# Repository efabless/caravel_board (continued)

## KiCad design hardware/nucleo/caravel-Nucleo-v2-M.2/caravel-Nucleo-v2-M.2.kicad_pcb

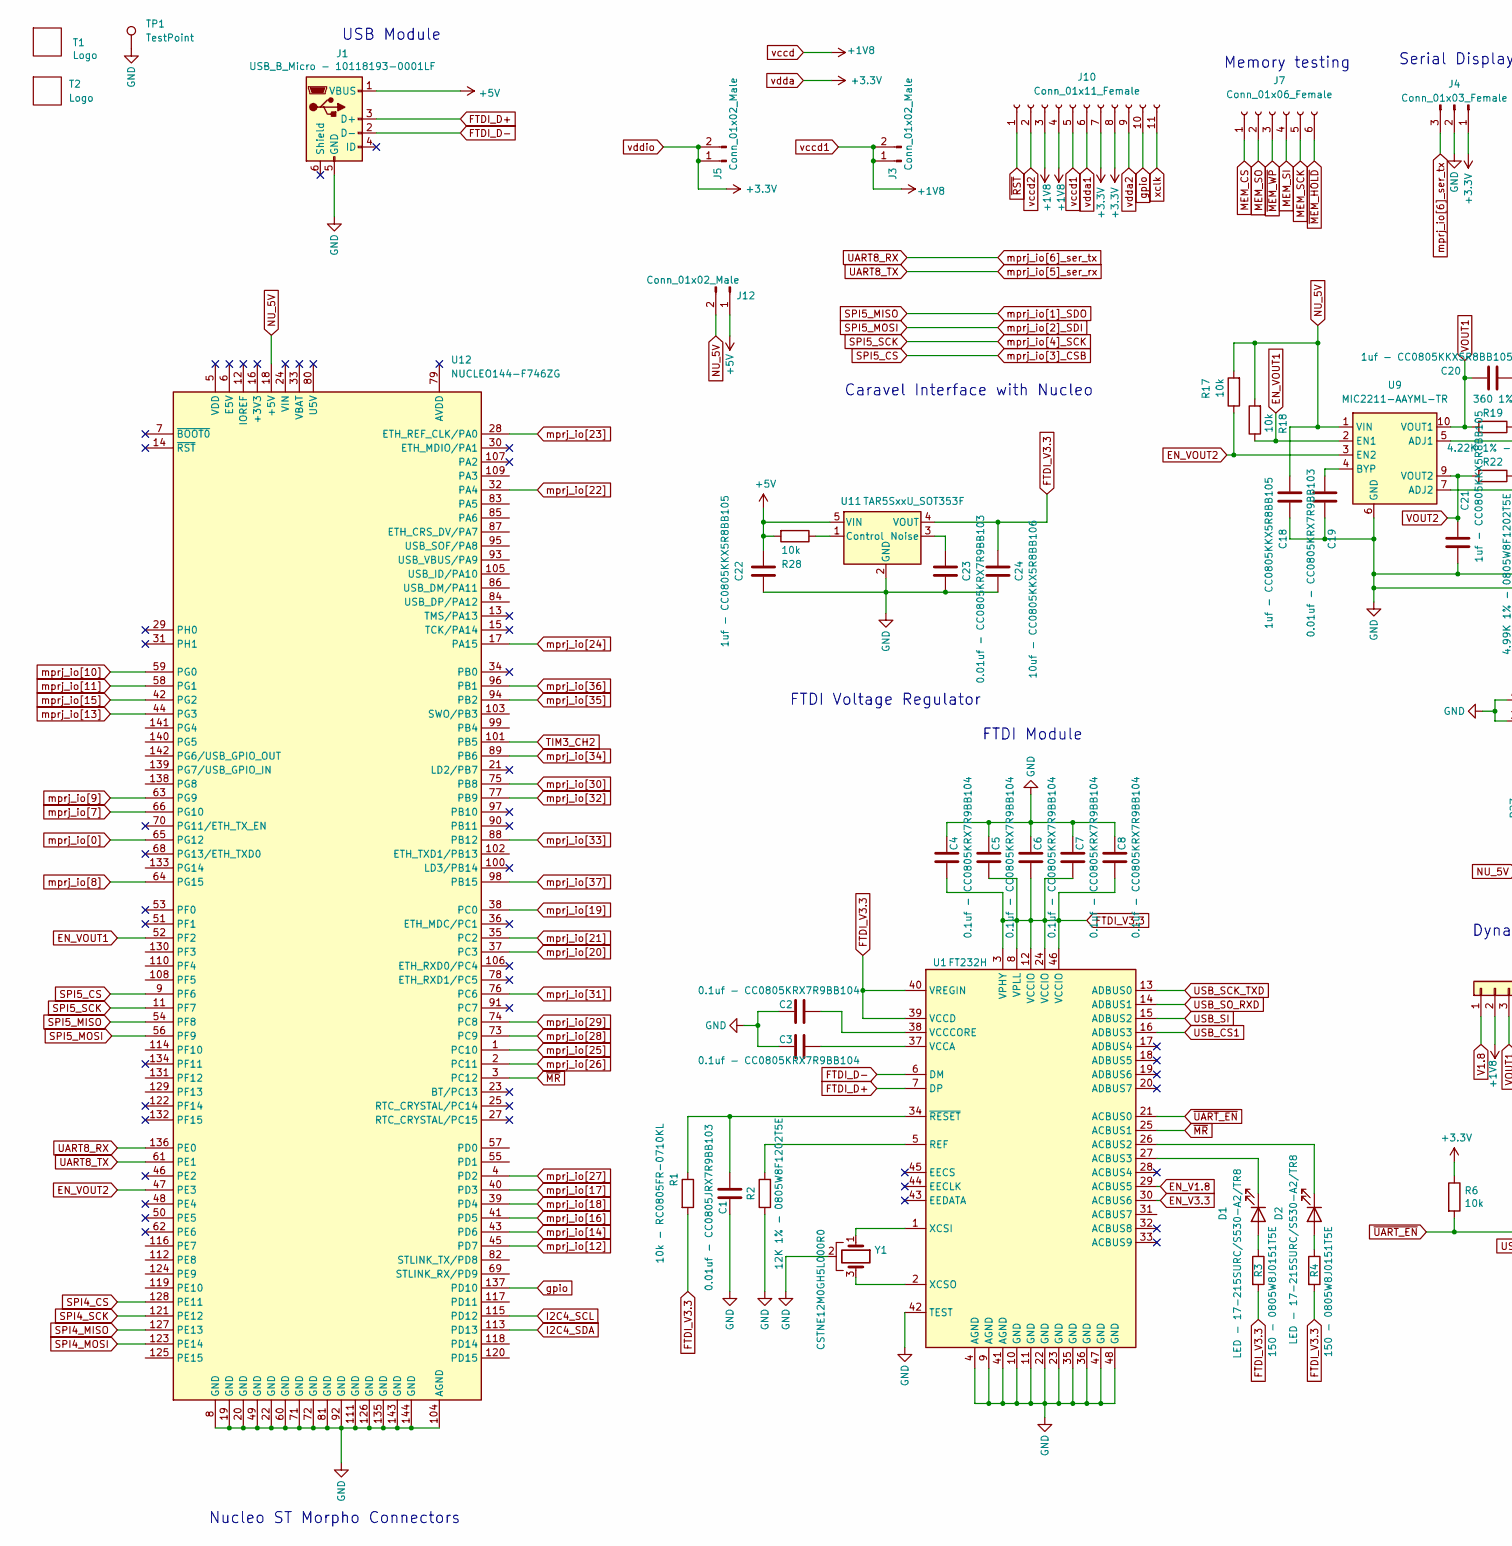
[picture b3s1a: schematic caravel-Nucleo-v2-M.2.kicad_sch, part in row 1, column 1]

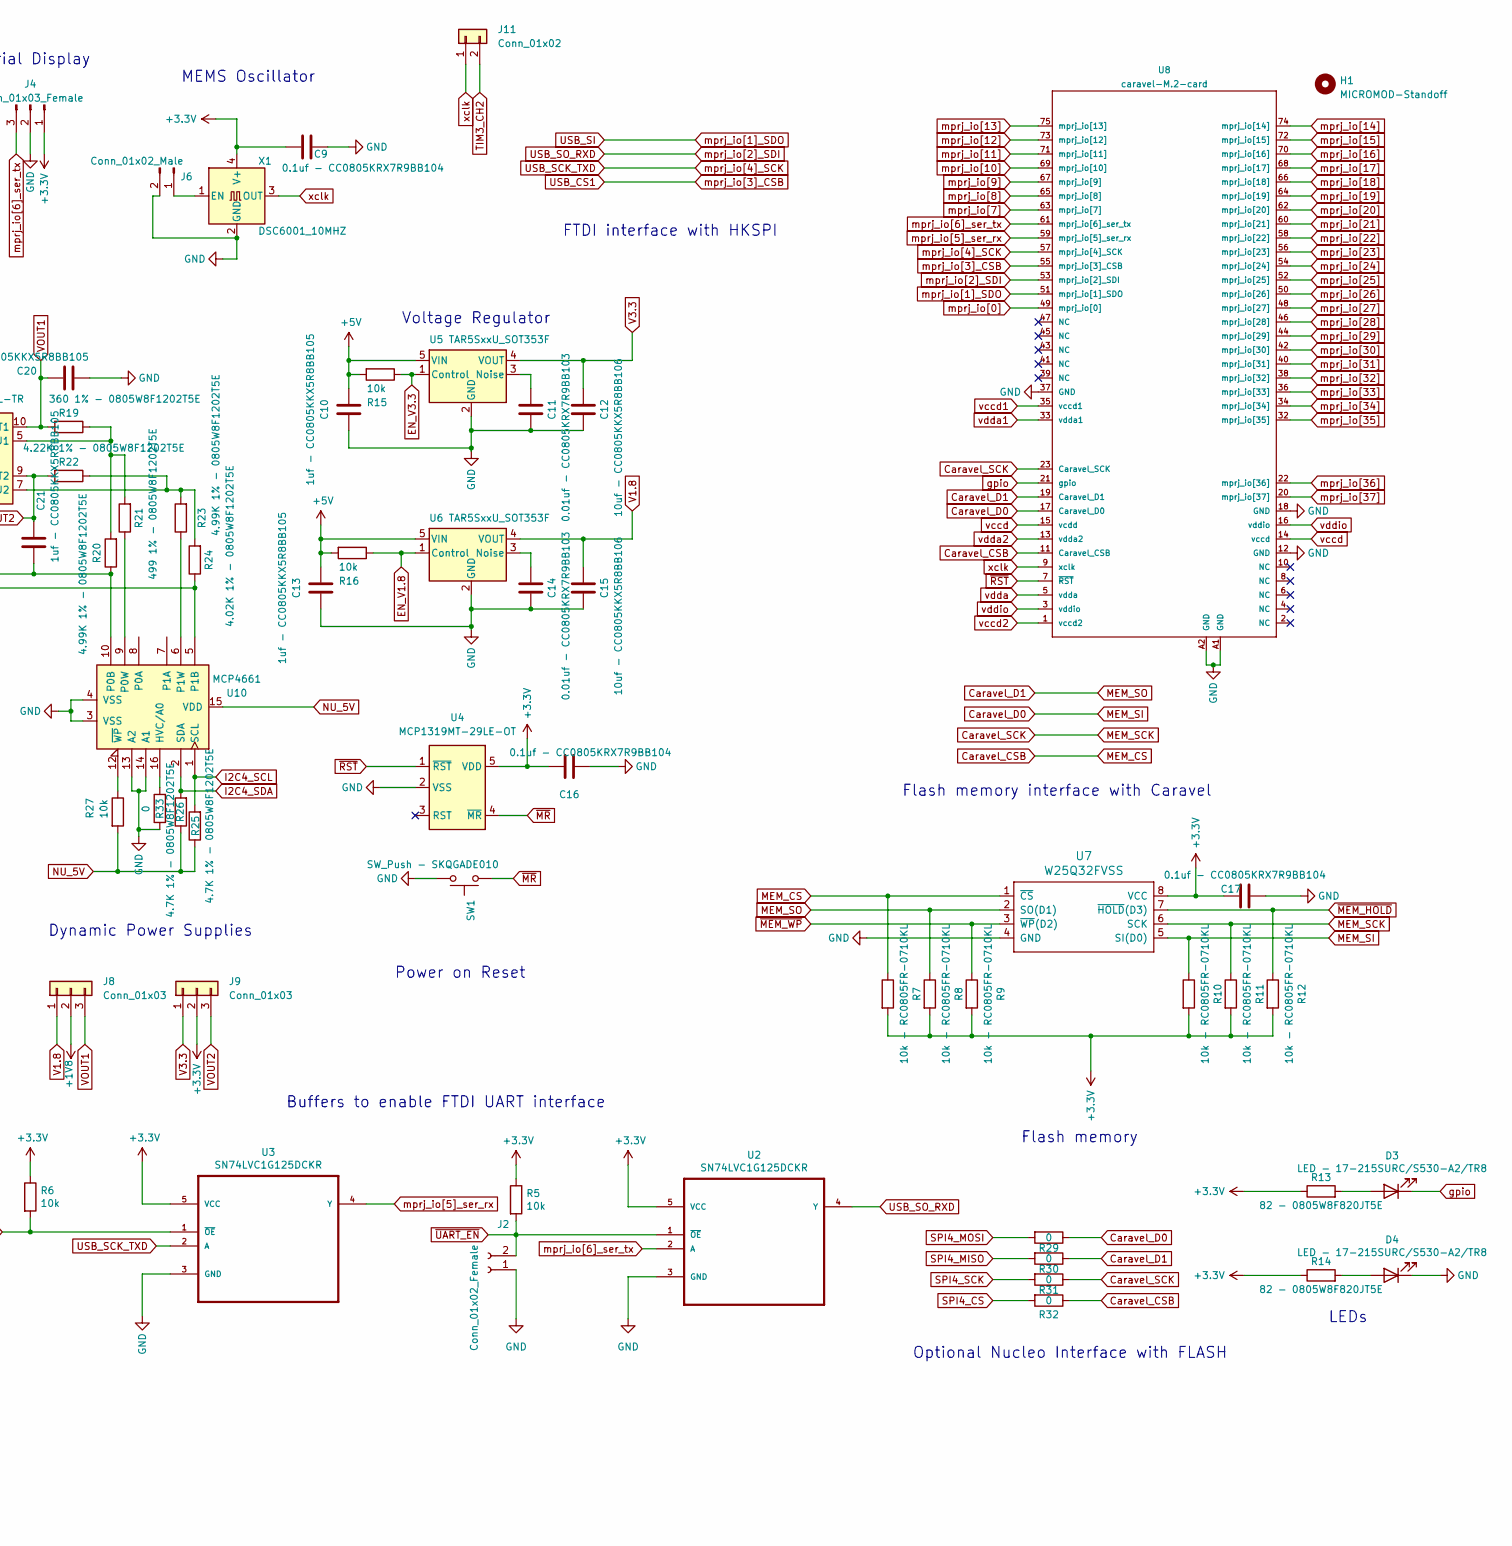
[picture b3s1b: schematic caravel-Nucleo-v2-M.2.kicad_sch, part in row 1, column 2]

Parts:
C1: 0.01uf - CC0805JRX7R9BB103; C_0805_2012Metric
C2, C3, C4, C5, C6, C7, C8, C9, C16, C17: 0.1uf - CC0805KRX7R9BB104; C_0805_2012Metric
C10, C13, C18, C20, C21, C22: 1uf - CC0805KKX5R8BB105; C_0805_2012Metric
C11, C14, C19, C23: 0.01uf - CC0805KRX7R9BB103; C_0805_2012Metric
C12, C15, C24: 10uf - CC0805KKX5R8BB106; C_0805_2012Metric
D1, D2, D3, D4: LED - 17-215SURC/S530-A2/TR8; LED_1206_3216Metric
H1: MICROMOD-Standoff; MicroMod-Standoff
J1: USB_B_Micro - 10118193-0001LF; FCI_10118193-0001LF
J2: Conn_01x02_Female; PinHeader_1x02_P2.54mm_Vertical
J3, J5, J6, J12: Conn_01x02_Male; PinHeader_1x02_P2.54mm_Vertical
J4: Conn_01x03_Female; PinHeader_1x03_P2.54mm_Vertical
J7: Conn_01x06_Female; PinHeader_1x06_P2.54mm_Vertical
J8, J9: Conn_01x03; PinHeader_1x03_P2.54mm_Vertical
J10: Conn_01x11_Female; PinHeader_1x11_P2.54mm_Vertical
J11: Conn_01x02; PinHeader_1x02_P2.54mm_Vertical
R1, R7, R8, R9, R10, R11, R12: 10k - RC0805FR-0710KL; R_0805_2012Metric
R2: 12K 1% - 0805W8F1202T5E; R_0805_2012Metric
R3, R4: 150 - 0805W8J0151T5E; R_0805_2012Metric
R5, R6, R15, R16, R17, R18, R27, R28: 10k; R_0805_2012Metric
R13, R14: 82 - 0805W8F820JT5E; R_0805_2012Metric
R19: 360 1% - 0805W8F1202T5E; R_0805_2012Metric
R20, R23: 4.99K 1% - 0805W8F1202T5E; R_0805_2012Metric
R21: 499 1% - 0805W8F1202T5E; R_0805_2012Metric
R22: 4.22K 1% - 0805W8F1202T5E; R_0805_2012Metric
R24: 4.02K 1% - 0805W8F1202T5E; R_0805_2012Metric
R25, R26: 4.7K 1% - 0805W8F1202T5E; R_0805_2012Metric
R29, R30, R31, R32, R33: 0; R_0805_2012Metric
SW1: SW_Push - SKQGADE010; SW4-SMD-5.2X5.2X1.5MM
T1: Logo; logo
T2: Logo; ef_logo
TP1: TestPoint; TestPoint_Bridge_Pitch2.54mm_Drill1.0mm
U1: FT232H; QFN-48-1EP_8x8mm_P0.5mm_EP6.2x6.2mm
U2, U3: SN74LVC1G125DCKR; SOT65P210X110-5N
U4: MCP1319MT-29LE-OT; PoR_5_SOT23
U5, U6, U11: TAR5SxxU_SOT353F; SOT-353F
U7: W25Q32FVSS; SOIC127P790X216-8N
U8: caravel-M.2-card; M.2-CONNECTOR-E
U9: MIC2211-AAYML-TR; DFN-10-1EP_3x3mm_P0.5mm_EP1.65x2.38mm
U10: MCP4661; QFN-16-1EP_5x5mm_P0.8mm_EP2.7x2.7mm
U12: NUCLEO144-F746ZG; ST_Morpho_Connector_144_STLink
X1: DSC6001_10MHZ; DSC6001JE1A-010.0000
Y1: CSTNE12M0GH5L000R0

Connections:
+5V: C10.2, C13.2, C22.2, J1.1 (VBUS), J12.1, R15.2, R16.2, R28.2, U5.5 (VIN), U6.5 (VIN), U11.5 (VIN)
Caravel_CSB: J7.1, R7.1, R32.1, U7.1 (~CS), U8.11 (Caravel_CSB)
Caravel_D0: J7.4, R10.1, R29.1, U7.5 (SI(D0)), U8.17 (Caravel_D0)
Caravel_D1: J7.2, R8.1, R30.1, U7.2 (SO(D1)), U8.19 (Caravel_D1)
Caravel_SCK: J7.5, R11.1, R31.1, U7.6 (SCK), U8.23 (Caravel_SCK)
EN_V1.8: R16.1, U1.29 (ACBUS5), U6.1 (Control)
EN_V3.3: R15.1, U1.30 (ACBUS6), U5.1 (Control)
EN_VOUT1: R18.1, U9.2 (EN1), U12.52 (PF2)
EN_VOUT2: R17.1, U9.3 (EN2), U12.47 (PE3)
FTDI_D+: J1.3 (D+), U1.7 (DP)
FTDI_D-: J1.2 (D-), U1.6 (DM)
FTDI_V3.3: C4.2, C5.2, C6.2, C7.2, C8.2, C24.2, R1.2, R3.2, R4.2, U1.3 (VPHY), U1.8 (VPLL), U1.12 (VCCIO), U1.24 (VCCIO), U1.39 (VCCD), U1.40 (VREGIN), U1.46 (VCCIO), U11.4 (VOUT)
GND: C1.1, C2.1, C3.1, C4.1, C5.1, C6.1, C7.1, C8.1, C9.1, C10.1, C11.2, C12.1, C13.1, C14.2, C15.1, C16.1, C17.2, C18.1, C19.2, C20.2, C21.2, C22.1, C23.2, C24.1, D4.1 (K), J1.5 (GND), J2.1, J4.2, J6.2, R2.1, R20.1, R24.1, R33.1, SW1.2, TP1.1, U1.4 (AGND), U1.9 (AGND), U1.10 (GND), U1.11 (GND), U1.22 (GND), U1.23 (GND), U1.35 (GND), U1.36 (GND), U1.41 (AGND), U1.42 (TEST), U1.47 (GND), U1.48 (GND), U2.3 (GND), U3.3 (GND), U4.2 (VSS), U5.2 (GND), U6.2 (GND), U7.4 (GND), U8.12 (GND), U8.18 (GND), U8.37 (GND), U8.A1 (GND), U8.A2 (GND), U9.6 (GND), U10.3 (VSS), U10.4 (VSS), U10.5 (P1B), U10.10 (P0B), U10.13 (A2), U10.14 (A1), U11.2 (GND), U12.8 (GND), U12.19 (GND), U12.20 (GND), U12.22 (GND), U12.49 (GND), U12.60 (GND), U12.71 (GND), U12.72 (GND), U12.81 (GND), U12.92 (GND), U12.104 (AGND), U12.111 (GND), U12.126 (GND), U12.135 (GND), U12.143 (GND), U12.144 (GND), X1.2 (GND), Y1.2
I2C4_SCL: R25.2, U10.1 (SCL), U12.115 (PD12)
I2C4_SDA: R26.2, U10.2 (SDA), U12.113 (PD13)
NU_5V: C18.2, J12.2, R17.2, R18.2, R25.1, R26.1, R27.2, U9.1 (VIN), U10.15 (VDD), U12.18 (+5V)
unnamed: D1.2 (A), R3.1
unnamed: D1.1 (K), U1.27 (ACBUS3)
unnamed: D2.2 (A), R4.1
unnamed: D2.1 (K), U1.26 (ACBUS2)
unnamed: D3.2 (A), R13.2
unnamed: D4.2 (A), R14.2
unnamed: J6.1, X1.1 (EN)
unnamed: R2.2, U1.5 (REF)
unnamed: C3.2, U1.37 (VCCA)
unnamed: C2.2, U1.38 (VCCCORE)
unnamed: U1.1 (XCSI), Y1.1
unnamed: U1.2 (XCSO), Y1.3
unnamed: C1.2, R1.1, U1.34 (~RESET)
unnamed: C11.1, U5.3 (Noise)
unnamed: C14.1, U6.3 (Noise)
unnamed: R19.1, R20.2, R21.2, U9.5 (ADJ1)
unnamed: R22.1, R23.2, R24.2, U9.7 (ADJ2)
unnamed: C19.1, U9.4 (BYP)
unnamed: R33.2, U10.16 (HVC/A0)
unnamed: R21.1, U10.9 (P0W)
unnamed: R23.1, U10.6 (P1W)
unnamed: R27.1, U10.12 (~WP)
unnamed: R28.1, U11.1 (Control)
unnamed: C23.1, U11.3 (Noise)
SPI4_CS: R32.2, U12.128 (PE11)
SPI4_MISO: R30.2, U12.127 (PE13)
SPI4_MOSI: R29.2, U12.123 (PE14)
SPI4_SCK: R31.2, U12.121 (PE12)
SPI5_CS: U1.16 (ADBUS3), U8.55 (mprj_io[3]_CSB), U12.9 (PF6)
SPI5_MISO: U1.15 (ADBUS2), U8.51 (mprj_io[1]_SDO), U12.54 (PF8)
SPI5_MOSI: U1.14 (ADBUS1), U2.4 (Y), U8.53 (mprj_io[2]_SDI), U12.56 (PF9)
SPI5_SCK: U1.13 (ADBUS0), U3.2 (A), U8.57 (mprj_io[4]_SCK), U12.11 (PF7)
TIM3_CH2: J11.2, U12.101 (PB5)
UART8_RX: J4.3, U2.2 (A), U8.61 (mprj_io[6]_ser_tx), U12.136 (PE0)
UART8_TX: U3.4 (Y), U8.59 (mprj_io[5]_ser_rx), U12.61 (PE1)
V1.8: C15.2, J8.1, U6.4 (VOUT)
V3.3: C12.2, J9.1, U5.4 (VOUT)
VOUT1: C20.1, J8.3, R19.2, U9.10 (VOUT1)
VOUT2: C21.1, J9.3, R22.2, U9.9 (VOUT2)
gpio: D3.1 (K), J10.10, U8.21 (gpio), U12.137 (PD10)
mprj_io[0]: U8.49 (mprj_io[0]), U12.65 (PG12)
mprj_io[7]: U8.63 (mprj_io[7]), U12.66 (PG10)
mprj_io[8]: U8.65 (mprj_io[8]), U12.64 (PG15)
mprj_io[9]: U8.67 (mprj_io[9]), U12.63 (PG9)
mprj_io[10]: U8.69 (mprj_io[10]), U12.59 (PG0)
mprj_io[11]: U8.71 (mprj_io[11]), U12.58 (PG1)
mprj_io[12]: U8.73 (mprj_io[12]), U12.45 (PD7)
mprj_io[13]: U8.75 (mprj_io[13]), U12.44 (PG3)
mprj_io[14]: U8.74 (mprj_io[14]), U12.43 (PD6)
mprj_io[15]: U8.72 (mprj_io[15]), U12.42 (PG2)
mprj_io[16]: U8.70 (mprj_io[16]), U12.41 (PD5)
mprj_io[17]: U8.68 (mprj_io[17]), U12.40 (PD3)
mprj_io[18]: U8.66 (mprj_io[18]), U12.39 (PD4)
mprj_io[19]: U8.64 (mprj_io[19]), U12.38 (PC0)
mprj_io[20]: U8.62 (mprj_io[20]), U12.37 (PC3)
mprj_io[21]: U8.60 (mprj_io[21]), U12.35 (PC2)
mprj_io[22]: U8.58 (mprj_io[22]), U12.32 (PA4)
mprj_io[23]: U8.56 (mprj_io[23]), U12.28 (ETH_REF_CLK/PA0)
mprj_io[24]: U8.54 (mprj_io[24]), U12.17 (PA15)
mprj_io[25]: U8.52 (mprj_io[25]), U12.1 (PC10)
mprj_io[26]: U8.50 (mprj_io[26]), U12.2 (PC11)
mprj_io[27]: U8.48 (mprj_io[27]), U12.4 (PD2)
mprj_io[28]: U8.46 (mprj_io[28]), U12.73 (PC9)
mprj_io[29]: U8.44 (mprj_io[29]), U12.74 (PC8)
mprj_io[30]: U8.42 (mprj_io[30]), U12.75 (PB8)
mprj_io[31]: U8.40 (mprj_io[31]), U12.76 (PC6)
mprj_io[32]: U8.38 (mprj_io[32]), U12.77 (PB9)
mprj_io[33]: U8.36 (mprj_io[33]), U12.88 (PB12)
mprj_io[34]: U8.34 (mprj_io[34]), U12.89 (PB6)
mprj_io[35]: U8.32 (mprj_io[35]), U12.94 (PB2)
mprj_io[36]: U8.22 (mprj_io[36]), U12.96 (PB1)
mprj_io[37]: U8.20 (mprj_io[37]), U12.98 (PB15)
vccd: J3.1, J3.2, J8.2, J10.3, J10.4, J10.5, U8.14 (vccd), U8.15 (vcdd), U8.35 (vccd1)
vccd2: J10.2, U8.1 (vccd2)
vdda: C9.2, C16.2, C17.1, J4.1, J5.1, J5.2, J9.2, J10.7, J10.8, R5.1, R6.1, R7.2, R8.2, R9.2, R10.2, R11.2, R12.2, R13.1, R14.1, U2.5 (VCC), U3.5 (VCC), U4.5 (VDD), U7.8 (VCC), U8.3 (vddio), U8.5 (vdda), U8.16 (vddio), X1.4 (V+)
vdda1: J10.6, U8.33 (vdda1)
vdda2: J10.9, U8.13 (vdda2)
xclk: J10.11, J11.1, U8.9 (xclk), X1.3 (OUT)
~MEM_HOLD: J7.6, R12.1, U7.7 (~HOLD(D3))
~MEM_WP: J7.3, R9.1, U7.3 (~WP(D2))
~MR: SW1.1, U1.25 (ACBUS1), U4.4 (~MR), U12.3 (PC12)
~RST: J10.1, U4.1 (~RST), U8.7 (~RST)
~UART_EN: J2.2, R5.2, R6.2, U1.21 (ACBUS0), U2.1 (~OE), U3.1 (~OE)

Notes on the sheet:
Caravel Interface with Nucleo
Flash memory
MEMS Oscillator
Serial Display
Power on Reset
LEDs
Memory testing
Voltage Regulator
Optional Nucleo Interface with FLASH
FTDI interface with HKSPI
USB Module
FTDI Module
FTDI Voltage Regulator
Buffers to enable FTDI UART interface
Nucleo ST Morpho Connectors
Flash memory interface with Caravel
Dynamic Power Supplies

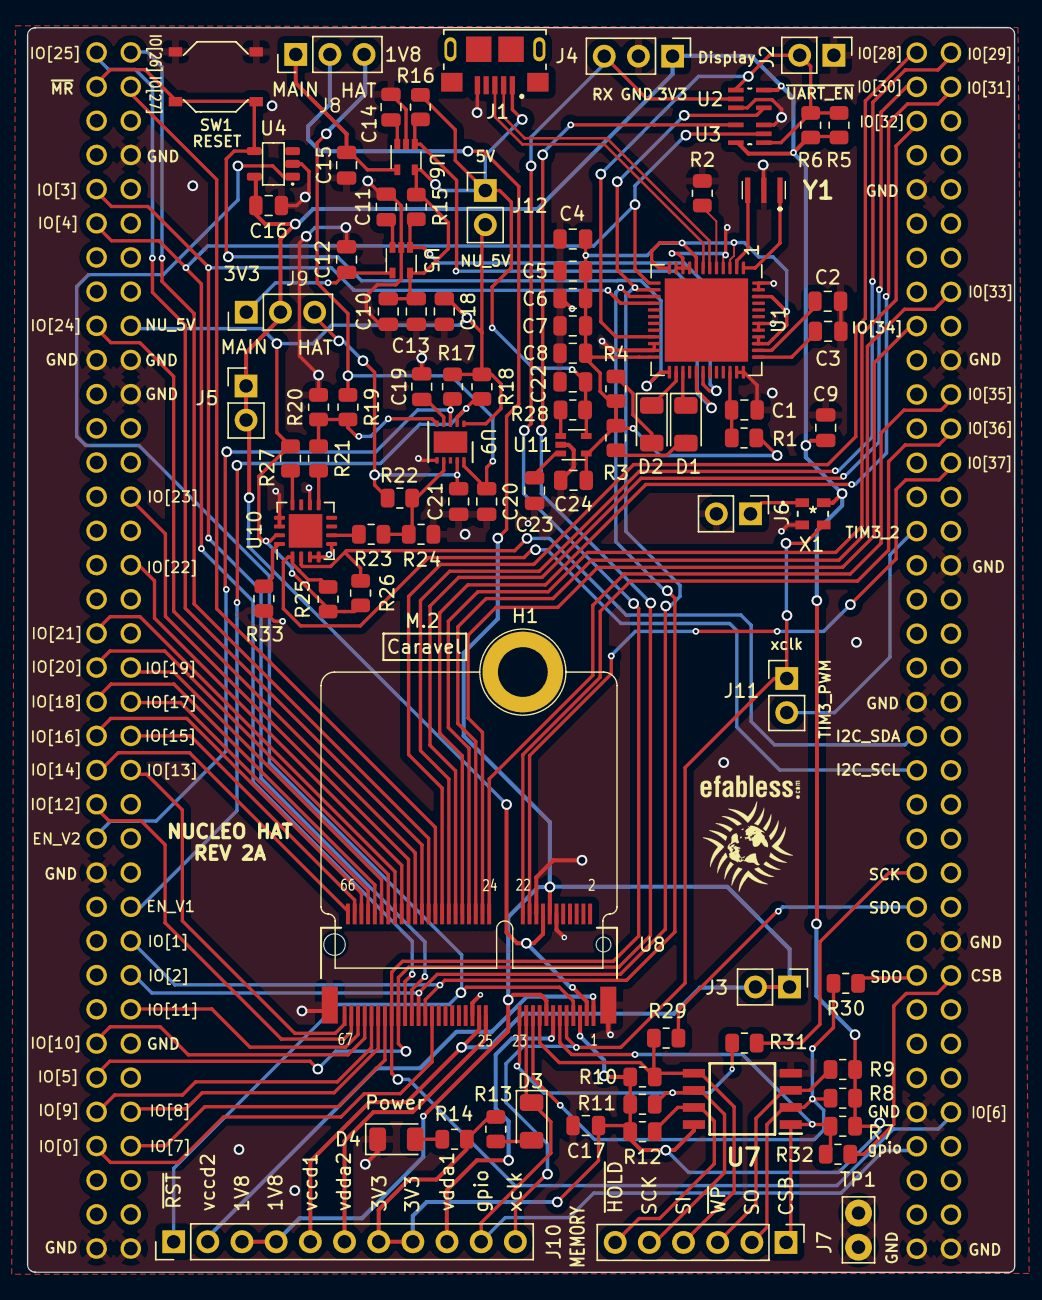
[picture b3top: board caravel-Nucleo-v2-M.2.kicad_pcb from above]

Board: 2 copper layers, 73.4 x 92.5 mm, 92 parts (0 on the bottom side), 99 nets.

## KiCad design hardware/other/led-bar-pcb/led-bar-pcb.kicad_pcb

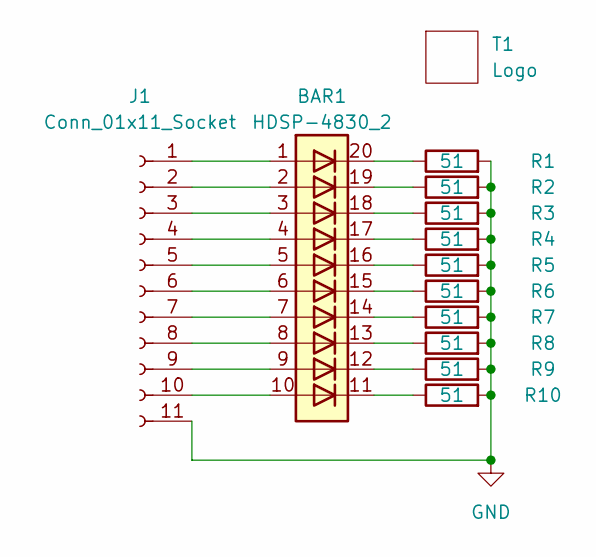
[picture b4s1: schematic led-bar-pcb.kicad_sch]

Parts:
BAR1: HDSP-4830_2; HDSP-4830
J1: Conn_01x11_Socket; PinHeader_1x11_P1.00mm_Vertical
R1, R2, R3, R4, R5, R6, R7, R8, R9, R10: 51; R_0805_2012Metric
T1: Logo; ef_logo

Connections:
GND: J1.11, R1.2, R2.2, R3.2, R4.2, R5.2, R6.2, R7.2, R8.2, R9.2, R10.2
unnamed: BAR1.11 (K), R10.1
unnamed: BAR1.12 (K), R9.1
unnamed: BAR1.13 (K), R8.1
unnamed: BAR1.14 (K), R7.1
unnamed: BAR1.15 (K), R6.1
unnamed: BAR1.16 (K), R5.1
unnamed: BAR1.17 (K), R4.1
unnamed: BAR1.18 (K), R3.1
unnamed: BAR1.19 (K), R2.1
unnamed: BAR1.20 (K), R1.1
unnamed: BAR1.1 (A), J1.1
unnamed: BAR1.2 (A), J1.2
unnamed: BAR1.3 (A), J1.3
unnamed: BAR1.4 (A), J1.4
unnamed: BAR1.5 (A), J1.5
unnamed: BAR1.6 (A), J1.6
unnamed: BAR1.7 (A), J1.7
unnamed: BAR1.8 (A), J1.8
unnamed: BAR1.9 (A), J1.9
unnamed: BAR1.10 (A), J1.10

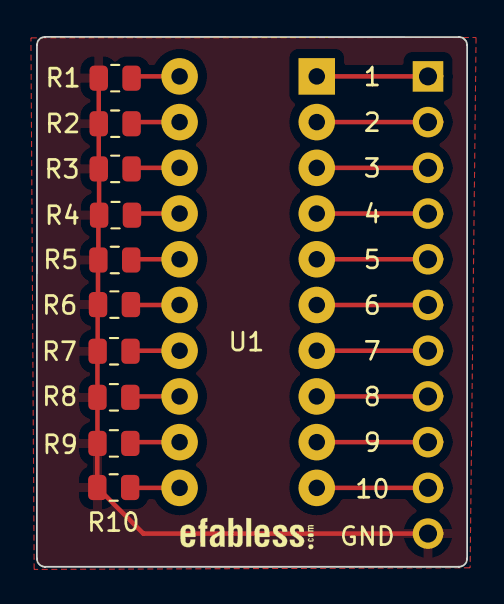
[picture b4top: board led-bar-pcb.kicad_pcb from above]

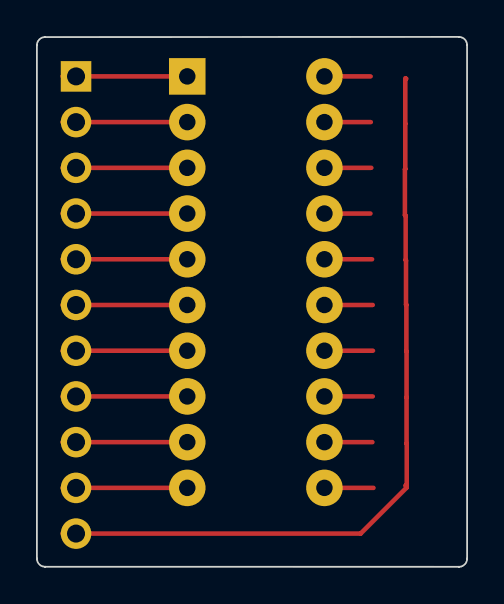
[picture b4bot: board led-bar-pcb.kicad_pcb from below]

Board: 2 copper layers, 23.9 x 29.4 mm, 13 parts (2 on the bottom side), 21 nets.

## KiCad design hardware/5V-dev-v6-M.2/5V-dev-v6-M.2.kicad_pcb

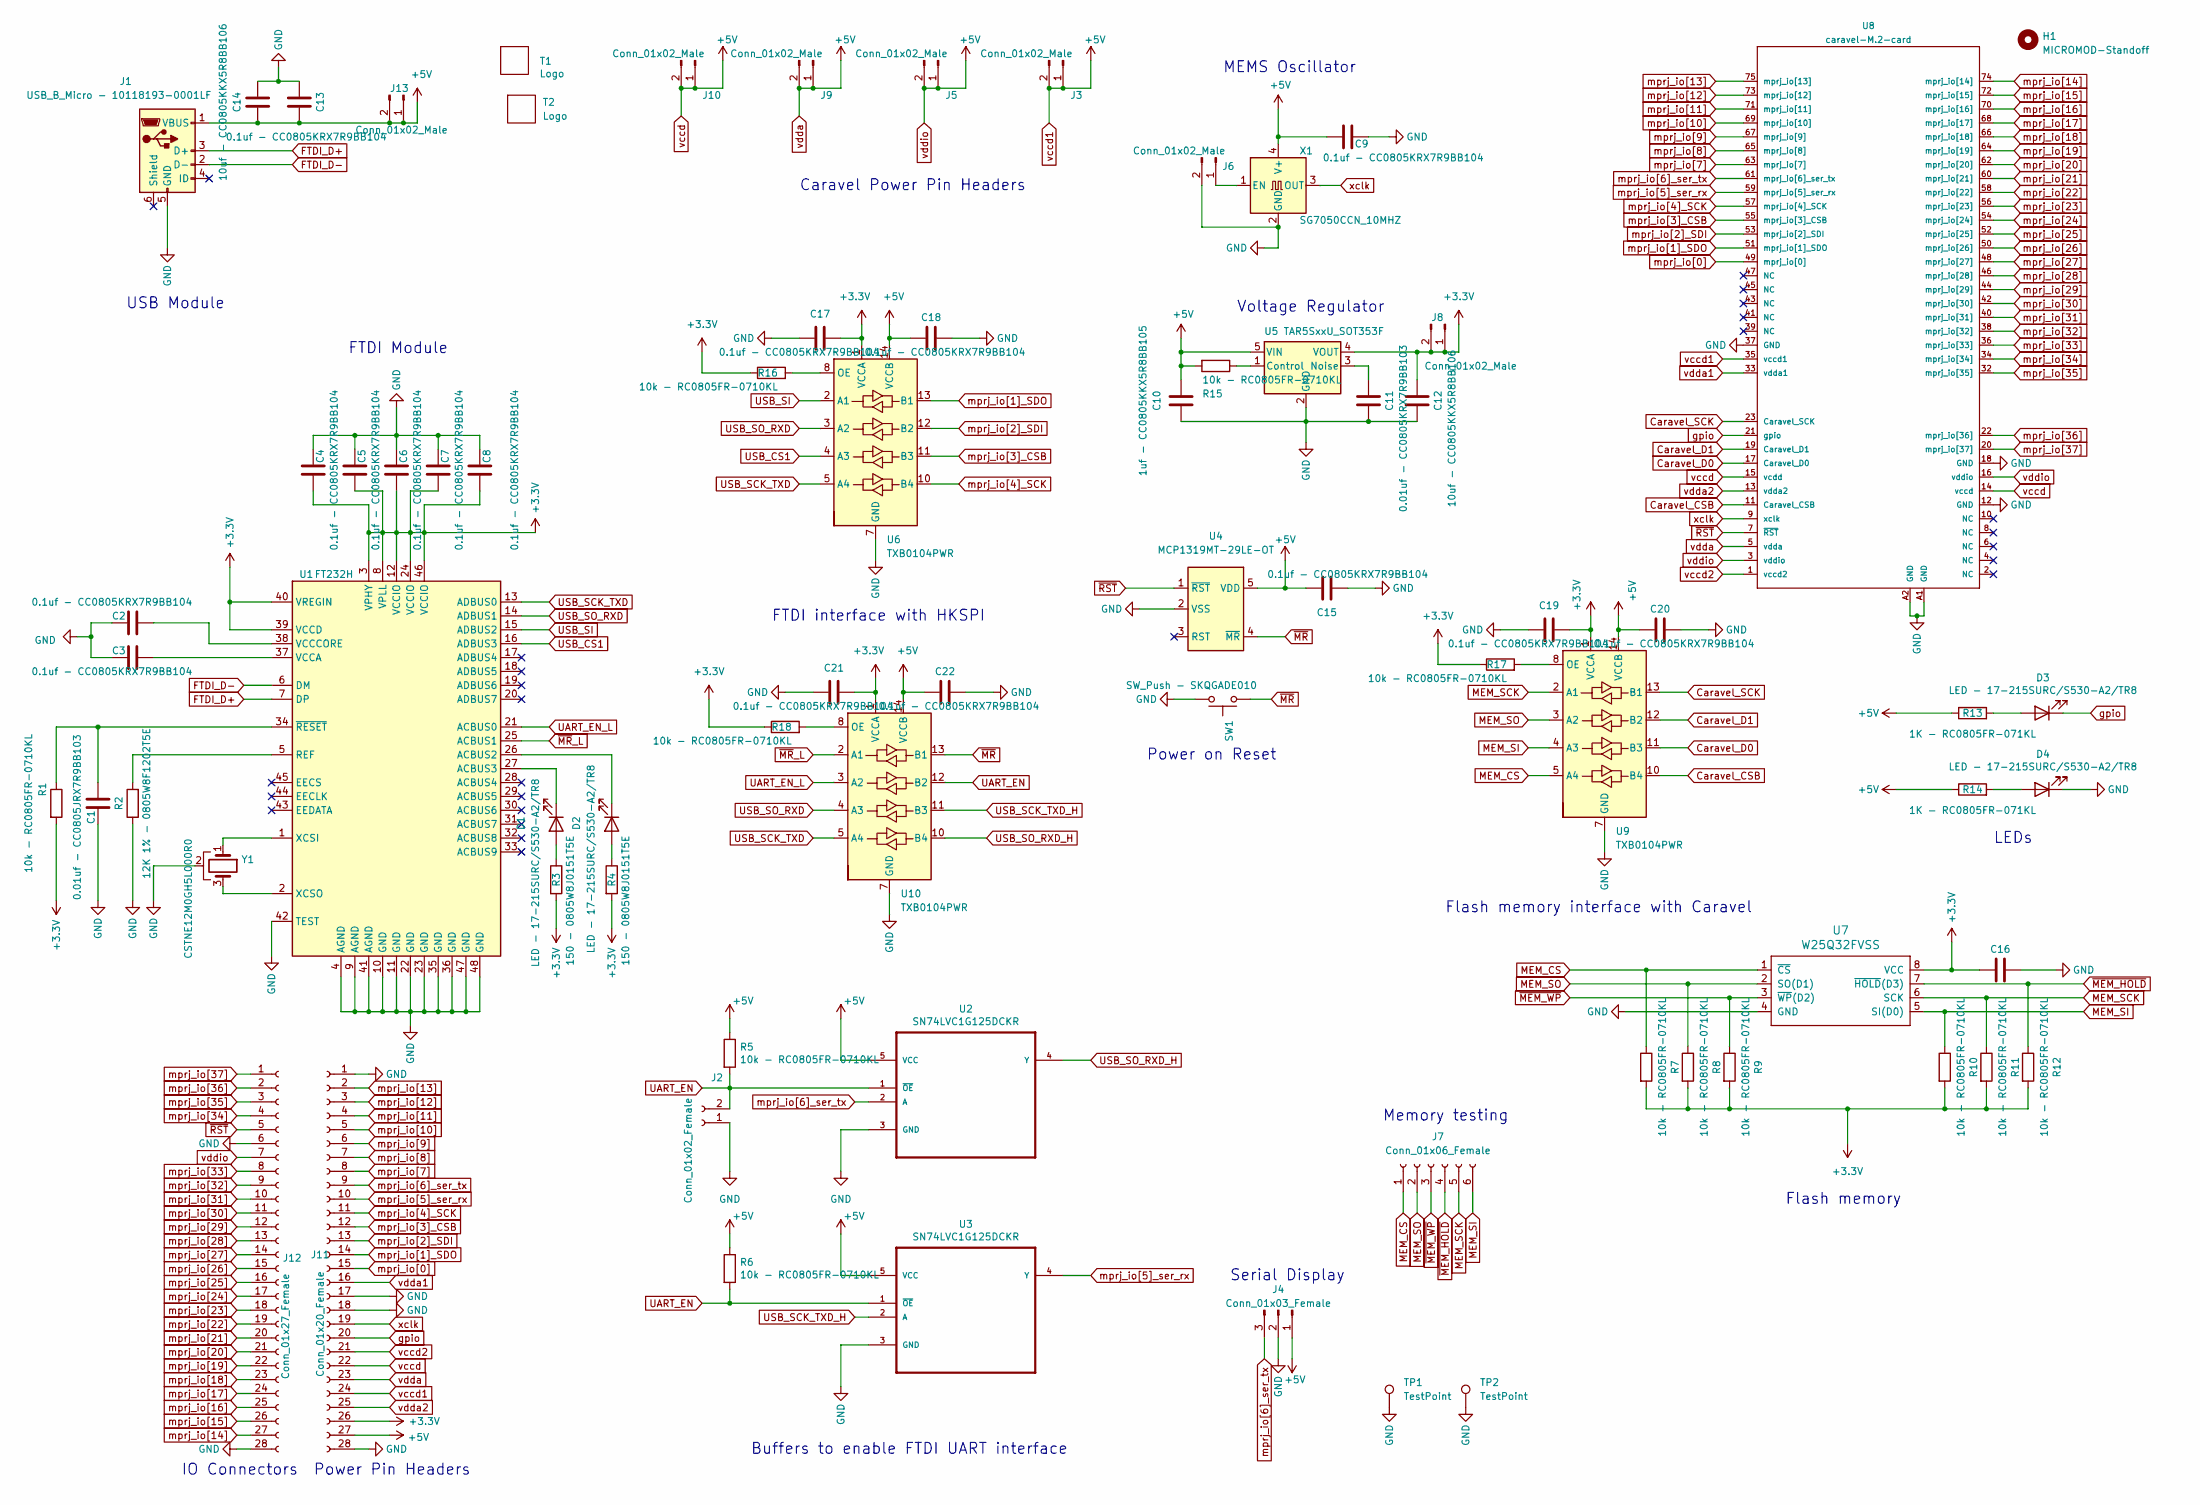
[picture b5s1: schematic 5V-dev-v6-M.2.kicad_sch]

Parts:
C1: 0.01uf - CC0805JRX7R9BB103; C_0805_2012Metric
C2, C3, C4, C5, C6, C7, C8, C9, C13, C15, C16, C17, C18, C19, C20, C21, C22: 0.1uf - CC0805KRX7R9BB104; C_0805_2012Metric
C10: 1uf - CC0805KKX5R8BB105; C_0805_2012Metric
C11: 0.01uf - CC0805KRX7R9BB103; C_0805_2012Metric
C12, C14: 10uf - CC0805KKX5R8BB106; C_0805_2012Metric
D1, D2, D3, D4: LED - 17-215SURC/S530-A2/TR8; LED_1206_3216Metric
H1: MICROMOD-Standoff; MicroMod-Standoff
J1: USB_B_Micro - 10118193-0001LF; FCI_10118193-0001LF
J2: Conn_01x02_Female; PinHeader_1x02_P2.54mm_Vertical
J3, J5, J6, J8, J9, J10, J13: Conn_01x02_Male; PinHeader_1x02_P2.54mm_Vertical
J4: Conn_01x03_Female; PinHeader_1x03_P2.54mm_Vertical
J7: Conn_01x06_Female; PinHeader_1x06_P2.54mm_Vertical
J11: Conn_01x20_Female; PinHeader_1x20_P2.54mm_Vertical
J12: Conn_01x27_Female; PinHeader_1x27_P2.54mm_Vertical
R1, R5, R6, R7, R8, R9, R10, R11, R12, R15, R16, R17, R18: 10k - RC0805FR-0710KL; R_0805_2012Metric
R2: 12K 1% - 0805W8F1202T5E; R_0805_2012Metric
R3, R4: 150 - 0805W8J0151T5E; R_0805_2012Metric
R13, R14: 1K - RC0805FR-071KL; R_0805_2012Metric
SW1: SW_Push - SKQGADE010; SW4-SMD-5.2X5.2X1.5MM
T1: Logo; logo
T2: Logo; ef_logo
TP1, TP2: TestPoint; TestPoint_Bridge_Pitch2.54mm_Drill1.0mm
U1: FT232H; QFN-48-1EP_8x8mm_P0.5mm_EP6.2x6.2mm
U2, U3: SN74LVC1G125DCKR; SOT65P210X110-5N
U4: MCP1319MT-29LE-OT; PoR_5_SOT23
U5: TAR5SxxU_SOT353F; SOT-353F
U6, U9, U10: TXB0104PWR; TSSOP-14_4.4x5mm_P0.65mm
U7: W25Q32FVSS; SOIC127P790X216-8N
U8: caravel-M.2-card; M.2-CONNECTOR-E
X1: SG7050CCN_10MHZ; SG7050CCN-10M-HJGA3
Y1: CSTNE12M0GH5L000R0

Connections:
+3.3V: C4.2, C5.2, C6.2, C7.2, C8.2, C12.2, C16.1, C17.2, C19.2, C21.2, J8.1, J8.2, J11.26, R1.2, R3.2, R4.2, R7.2, R8.2, R9.2, R10.2, R11.2, R12.2, R16.1, R17.1, R18.1, U1.3 (VPHY), U1.8 (VPLL), U1.12 (VCCIO), U1.24 (VCCIO), U1.39 (VCCD), U1.40 (VREGIN), U1.46 (VCCIO), U5.4 (VOUT), U6.1 (VCCA), U7.8 (VCC), U9.1 (VCCA), U10.1 (VCCA)
Caravel_CSB: U8.11 (Caravel_CSB), U9.10 (B4)
Caravel_D0: U8.17 (Caravel_D0), U9.11 (B3)
Caravel_D1: U8.19 (Caravel_D1), U9.12 (B2)
Caravel_SCK: U8.23 (Caravel_SCK), U9.13 (B1)
FTDI_D+: J1.3 (D+), U1.7 (DP)
FTDI_D-: J1.2 (D-), U1.6 (DM)
GND: C1.1, C2.1, C3.1, C4.1, C5.1, C6.1, C7.1, C8.1, C9.1, C10.1, C11.2, C12.1, C13.2, C14.1, C15.1, C16.2, C17.1, C18.1, C19.1, C20.1, C21.1, C22.1, D4.1 (K), J1.5 (GND), J2.1, J4.2, J6.2, J11.1, J11.17, J11.18, J11.28, J12.6, J12.28, R2.1, SW1.2, TP1.1, TP2.1, U1.4 (AGND), U1.9 (AGND), U1.10 (GND), U1.11 (GND), U1.22 (GND), U1.23 (GND), U1.35 (GND), U1.36 (GND), U1.41 (AGND), U1.42 (TEST), U1.47 (GND), U1.48 (GND), U2.3 (GND), U3.3 (GND), U4.2 (VSS), U5.2 (GND), U6.7 (GND), U7.4 (GND), U8.12 (GND), U8.18 (GND), U8.37 (GND), U8.A1 (GND), U8.A2 (GND), U9.7 (GND), U10.7 (GND), X1.2 (GND), Y1.2
MEM_CS: J7.1, R7.1, U7.1 (~CS), U9.5 (A4)
MEM_SCK: J7.5, R11.1, U7.6 (SCK), U9.2 (A1)
MEM_SI: J7.6, R10.1, U7.5 (SI(D0)), U9.4 (A3)
MEM_SO: J7.2, R8.1, U7.2 (SO(D1)), U9.3 (A2)
unnamed: D1.2 (A), R3.1
unnamed: D1.1 (K), U1.27 (ACBUS3)
unnamed: D2.2 (A), R4.1
unnamed: D2.1 (K), U1.26 (ACBUS2)
unnamed: D3.2 (A), R13.2
unnamed: D4.2 (A), R14.2
unnamed: J6.1, X1.1 (EN)
unnamed: R2.2, U1.5 (REF)
unnamed: C3.2, U1.37 (VCCA)
unnamed: C2.2, U1.38 (VCCCORE)
unnamed: U1.1 (XCSI), Y1.1
unnamed: U1.2 (XCSO), Y1.3
unnamed: C1.2, R1.1, U1.34 (~RESET)
unnamed: R15.1, U5.1 (Control)
unnamed: C11.1, U5.3 (Noise)
unnamed: R16.2, U6.8 (OE)
unnamed: R17.2, U9.8 (OE)
unnamed: R18.2, U10.8 (OE)
UART_EN: J2.2, R5.2, R6.2, U2.1 (~OE), U3.1 (~OE), U10.12 (B2)
UART_EN_L: U1.21 (ACBUS0), U10.3 (A2)
USB_CS1: U1.16 (ADBUS3), U6.4 (A3)
USB_SCK_TXD: U1.13 (ADBUS0), U6.5 (A4), U10.5 (A4)
USB_SCK_TXD_H: U3.2 (A), U10.11 (B3)
USB_SI: U1.15 (ADBUS2), U6.2 (A1)
USB_SO_RXD: U1.14 (ADBUS1), U6.3 (A2), U10.4 (A3)
USB_SO_RXD_H: U2.4 (Y), U10.10 (B4)
gpio: D3.1 (K), J11.20, U8.21 (gpio)
mprj_io[0]: J11.15, U8.49 (mprj_io[0])
mprj_io[1]_SDO: J11.14, U6.13 (B1), U8.51 (mprj_io[1]_SDO)
mprj_io[2]_SDI: J11.13, U6.12 (B2), U8.53 (mprj_io[2]_SDI)
mprj_io[3]_CSB: J11.12, U6.11 (B3), U8.55 (mprj_io[3]_CSB)
mprj_io[4]_SCK: J11.11, U6.10 (B4), U8.57 (mprj_io[4]_SCK)
mprj_io[5]_ser_rx: J11.10, U3.4 (Y), U8.59 (mprj_io[5]_ser_rx)
mprj_io[6]_ser_tx: J4.3, J11.9, U2.2 (A), U8.61 (mprj_io[6]_ser_tx)
mprj_io[7]: J11.8, U8.63 (mprj_io[7])
mprj_io[8]: J11.7, U8.65 (mprj_io[8])
mprj_io[9]: J11.6, U8.67 (mprj_io[9])
mprj_io[10]: J11.5, U8.69 (mprj_io[10])
mprj_io[11]: J11.4, U8.71 (mprj_io[11])
mprj_io[12]: J11.3, U8.73 (mprj_io[12])
mprj_io[13]: J11.2, U8.75 (mprj_io[13])
mprj_io[14]: J12.27, U8.74 (mprj_io[14])
mprj_io[15]: J12.26, U8.72 (mprj_io[15])
mprj_io[16]: J12.25, U8.70 (mprj_io[16])
mprj_io[17]: J12.24, U8.68 (mprj_io[17])
mprj_io[18]: J12.23, U8.66 (mprj_io[18])
mprj_io[19]: J12.22, U8.64 (mprj_io[19])
mprj_io[20]: J12.21, U8.62 (mprj_io[20])
mprj_io[21]: J12.20, U8.60 (mprj_io[21])
mprj_io[22]: J12.19, U8.58 (mprj_io[22])
mprj_io[23]: J12.18, U8.56 (mprj_io[23])
mprj_io[24]: J12.17, U8.54 (mprj_io[24])
mprj_io[25]: J12.16, U8.52 (mprj_io[25])
mprj_io[26]: J12.15, U8.50 (mprj_io[26])
mprj_io[27]: J12.14, U8.48 (mprj_io[27])
mprj_io[28]: J12.13, U8.46 (mprj_io[28])
mprj_io[29]: J12.12, U8.44 (mprj_io[29])
mprj_io[30]: J12.11, U8.42 (mprj_io[30])
mprj_io[31]: J12.10, U8.40 (mprj_io[31])
mprj_io[32]: J12.9, U8.38 (mprj_io[32])
mprj_io[33]: J12.8, U8.36 (mprj_io[33])
mprj_io[34]: J12.4, U8.34 (mprj_io[34])
mprj_io[35]: J12.3, U8.32 (mprj_io[35])
mprj_io[36]: J12.2, U8.22 (mprj_io[36])
mprj_io[37]: J12.1, U8.20 (mprj_io[37])
vccd: C9.2, C10.2, C13.1, C14.2, C15.2, C18.2, C20.2, C22.2, J1.1 (VBUS), J3.1, J3.2, J4.1, J5.1, J5.2, J9.1, J9.2, J10.1, J10.2, J11.22, J11.23, J11.24, J11.27, J12.7, J13.1, J13.2, R5.1, R6.1, R13.1, R14.1, R15.2, U2.5 (VCC), U3.5 (VCC), U4.5 (VDD), U5.5 (VIN), U6.14 (VCCB), U8.3 (vddio), U8.5 (vdda), U8.14 (vccd), U8.15 (vcdd), U8.16 (vddio), U8.35 (vccd1), U9.14 (VCCB), U10.14 (VCCB), X1.4 (V+)
vccd2: J11.21, U8.1 (vccd2)
vdda1: J11.16, U8.33 (vdda1)
vdda2: J11.25, U8.13 (vdda2)
xclk: J11.19, U8.9 (xclk), X1.3 (OUT)
~MEM_HOLD: J7.4, R12.1, U7.7 (~HOLD(D3))
~MEM_WP: J7.3, R9.1, U7.3 (~WP(D2))
~MR: SW1.1, U4.4 (~MR), U10.13 (B1)
~MR_L: U1.25 (ACBUS1), U10.2 (A1)
~RST: J12.5, U4.1 (~RST), U8.7 (~RST)

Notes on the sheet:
Serial Display
Flash memory interface with Caravel
Caravel Power Pin Headers
Power on Reset
Flash memory
Memory testing
FTDI interface with HKSPI
Power Pin Headers
LEDs
Voltage Regulator
IO Connectors
FTDI Module
USB Module
MEMS Oscillator
Buffers to enable FTDI UART interface

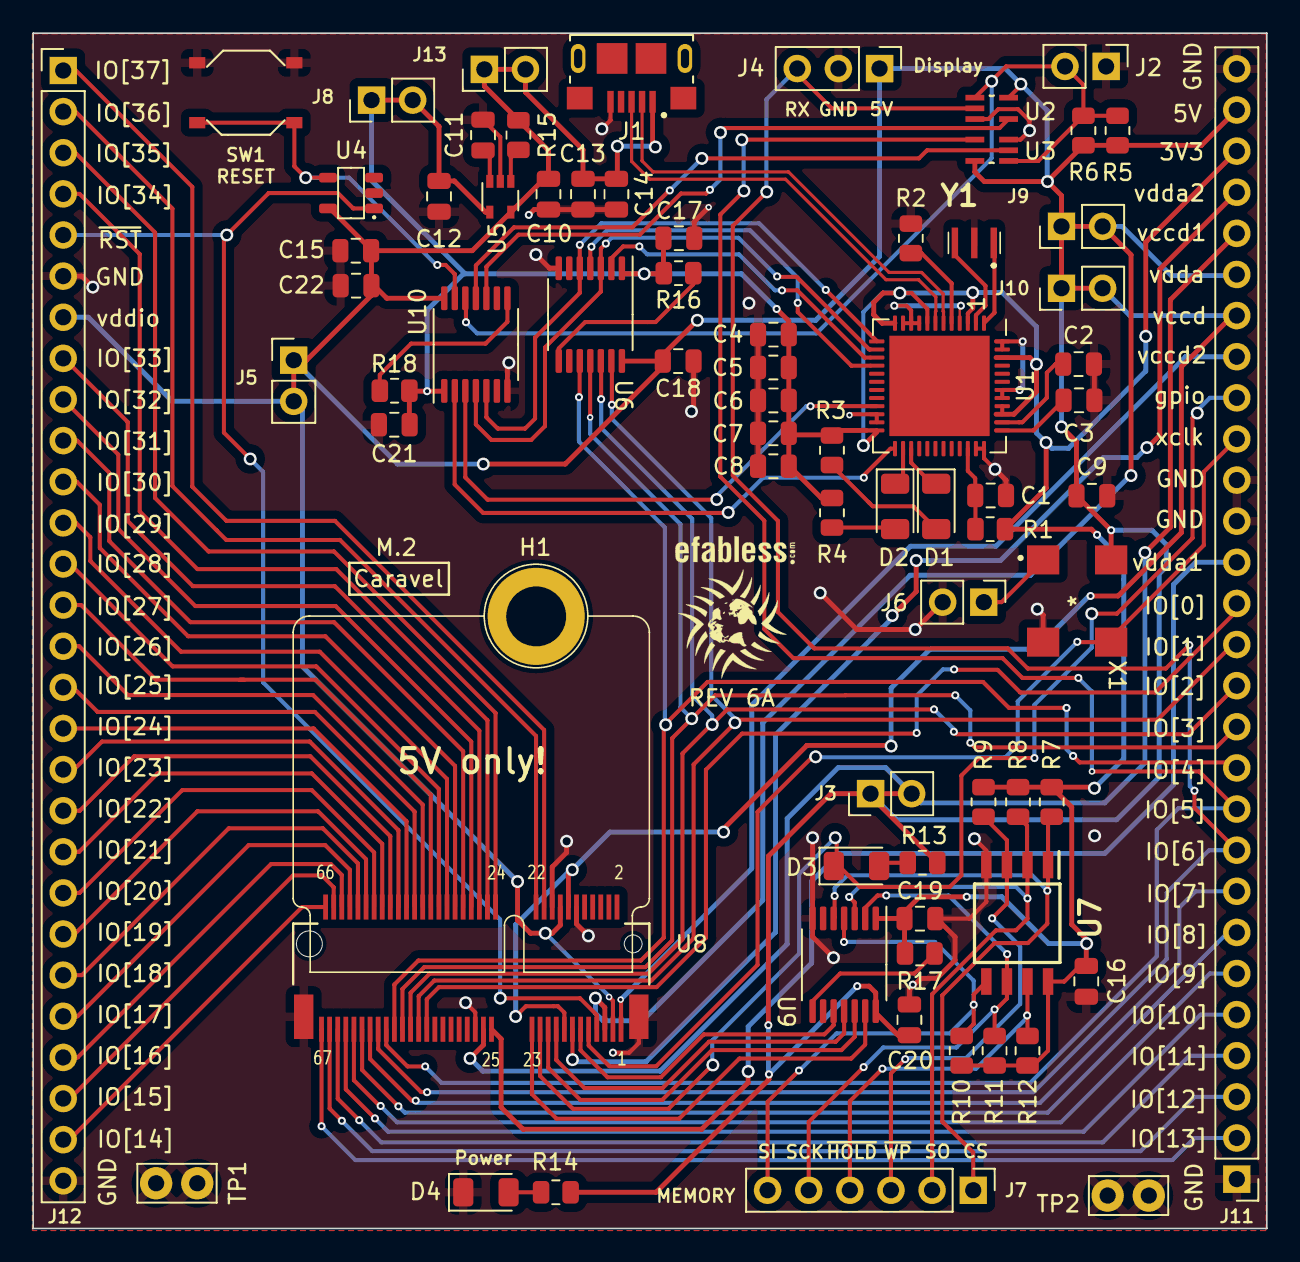
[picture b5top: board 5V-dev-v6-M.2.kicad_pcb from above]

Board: 2 copper layers, 76.2 x 73.8 mm, 75 parts (0 on the bottom side), 87 nets.
